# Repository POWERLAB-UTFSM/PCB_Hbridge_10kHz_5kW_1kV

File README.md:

# Proyecto PCB Hbridge

## Descripción

Repositorio con archivos necesarios para visualizar el esquematico y PCB del circuito Hbridge

## Requisitos

### Software

* KiCad, para diseño de esquemático y conversión a placa de circuito impreso
* Git, para control de versiones y manejo de repositorios.

## Contenido de carpetas:

* [PCB_Hbridge](PCB_Hbridge): Carpeta con archivos relacionados al esquematico y 
    * [BOM](PCB_Hbridge/BOM): Carpeta con lista detallada de todos los componentes electrónicos necesarios para construir un circuito impreso (PCB) obtenida directamente desde el software.
    * [GERBER](PCB_Hbridge/GERBER): Carpeta con archivos necesarios para la fabricación de la PCB.

* [BOM_v1](BOM_v1): Lista detallada con los componentes y su precio, dando un estimado del presupuesto necesario para su fabricación.

* [Documento_de_diseno](Documento_de_diseno): Documento que respalda el diseño y desarrollo del circuito implementado en la PCB

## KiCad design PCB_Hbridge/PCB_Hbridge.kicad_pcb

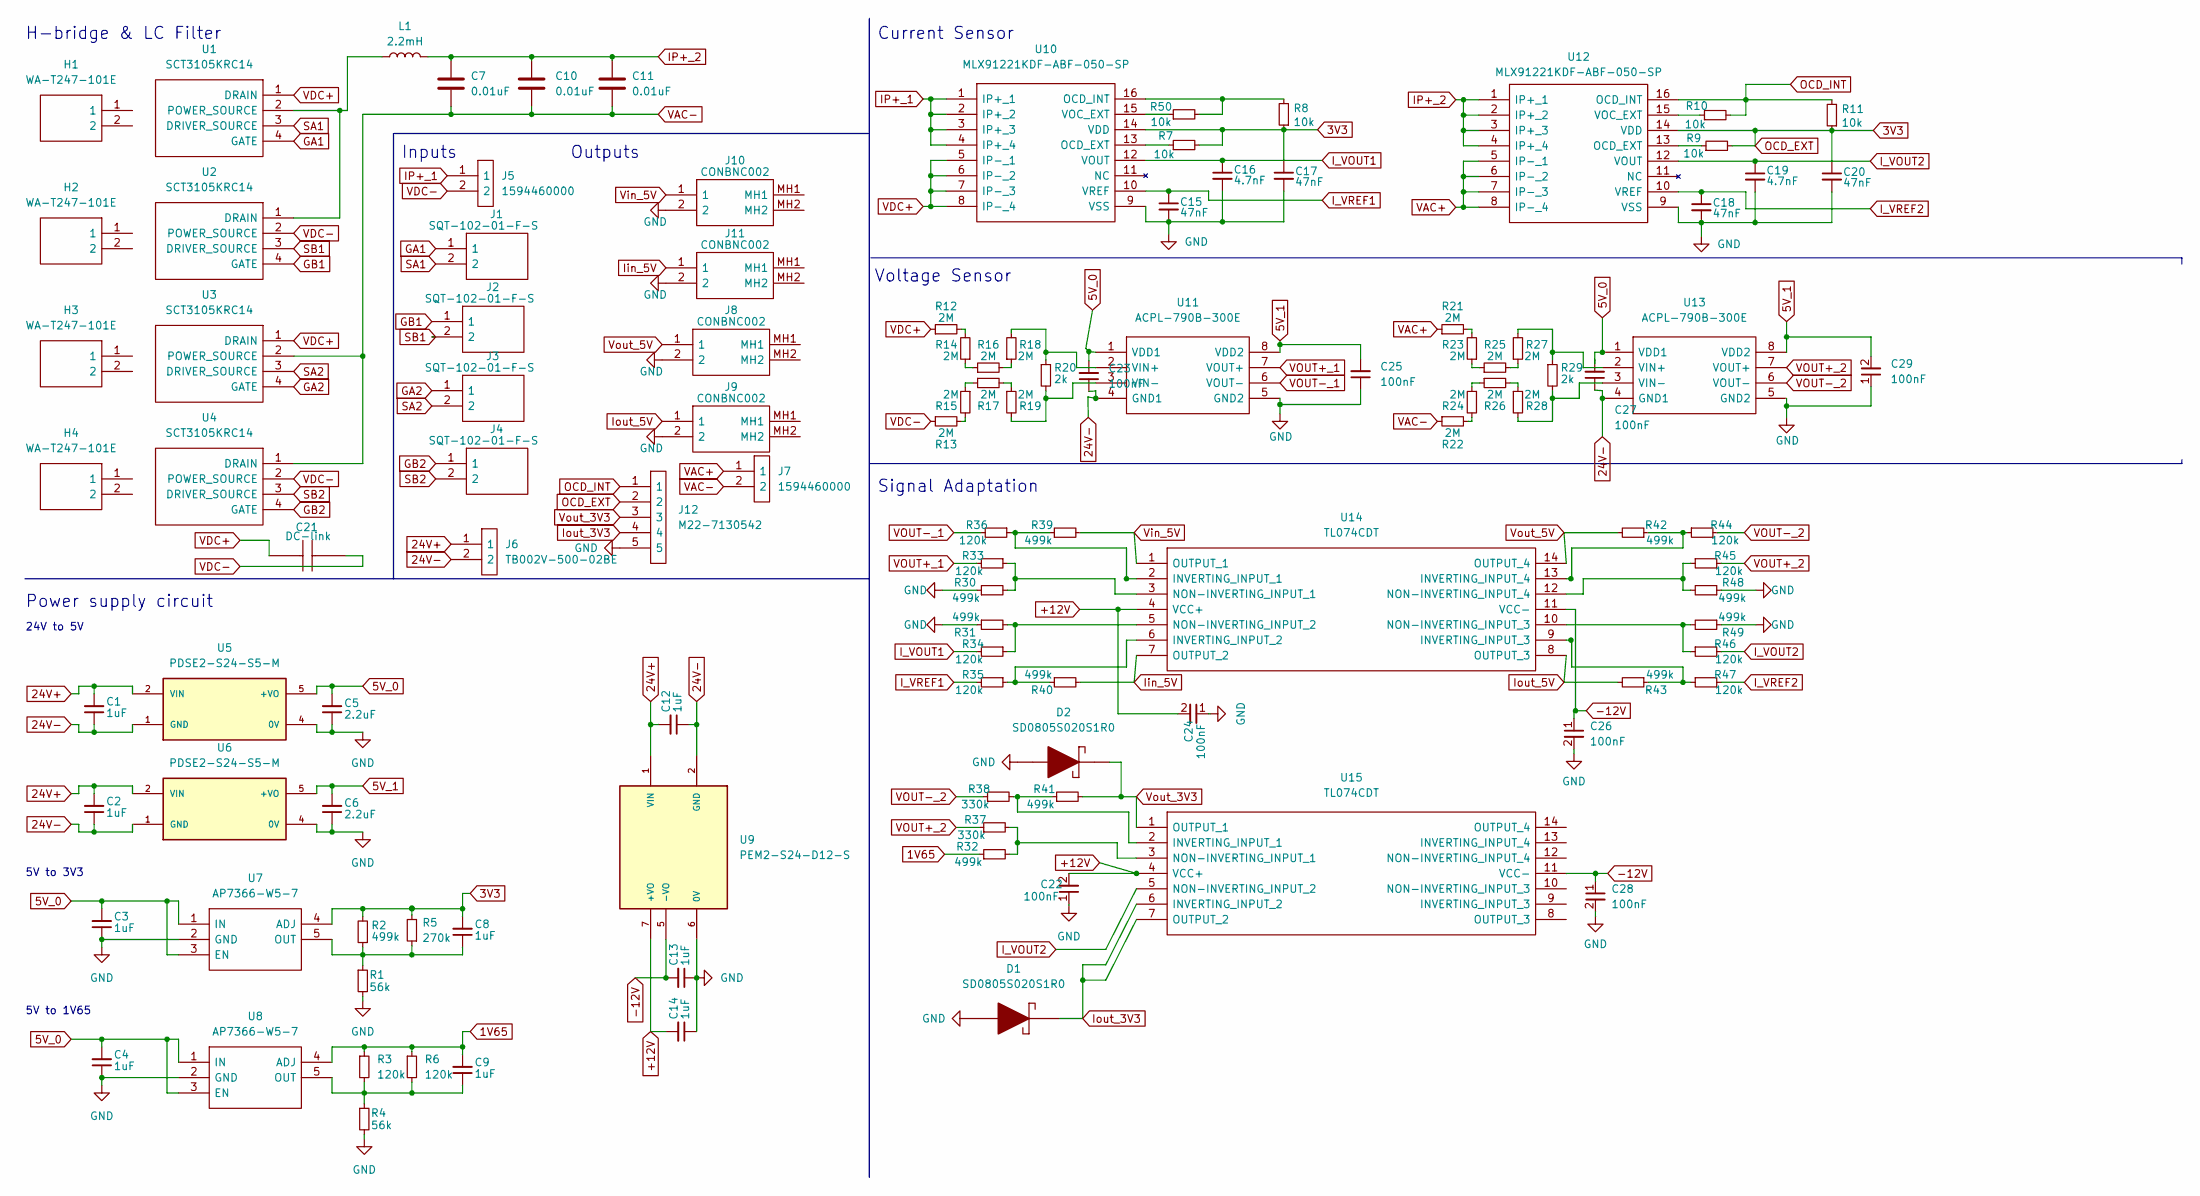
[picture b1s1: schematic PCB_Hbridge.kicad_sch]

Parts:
C1, C2, C3, C4, C8, C9, C12, C13, C14: 1uF; CAPC2012X145N_01uF; Manufacturer_Part_Number AC0805KFX7R9BB105
C5, C6: 2.2uF; CAPC3116X180N_2_2uF; Mouser Part Number 81-GCM31CR71H225KA5K
C7, C10, C11: 0.01uF; S103M69Z5UP63K7R
C15, C17, C18, C20: 47nF; CAPC3216X175N_47nF; Mouser Part Number 80-C1206C561KDGAUTO
C16, C19: 4.7nF; CAPC2012X94N_4_7nF; Mouser Part Number 581-0805ZC472KAT2A
C21: DC-link; C2225_DCLINK; Mouser Part Number 80-C2225C104KFR
C22, C23, C24, C25, C26, C27, C28, C29: 100nF; CAPC1005X55N_100nF; Mouser Part Number 810-CGA2B3X7R1V104K
D1, D2: SD0805S020S1R0; DIOM1613X100N; Mouser Part Number 581-SD0805S020S1R0
H1, H2, H3, H4: WA-T247-101E; WAT247101E; Mouser Part Number 588-WA-T247-101E
J1, J2, J3, J4: SQT-102-01-F-S; SQT-102-01-XX-S; Mouser Part Number 200-SQT10201FS
J5, J7: 1594460000; Mouser Part Number 470-1594460000
J6: TB002V-500-02BE; TB002V50002BE; Mouser Part Number 490-TB002V-500-02BE
J8, J9, J10, J11: CONBNC002; Mouser Part Number 712-CONBNC002
J12: M22-7130542; RHDR5W50P0X200_1X5_1050X240X440P; Mouser Part Number 855-M22-7130542
L1: 2.2mH; L_Toroid_Horizontal_D69.1mm_P63.20mm_Vishay_TJ9; Manufacturer_Part_Number TJ92UEB222L; Mouser Path Number 70-TJ92UEB222L
R1, R4: 56k; RESC2012X60N_56k; Mouser Part Number 652-CR0805FX-5602ELF
R2, R30, R31, R32, R39, R40, R41, R42, R43, R48, R49: 499k; RESC2012X60N_499k; Mouser Part Number 652-CR0805FX-5602ELF
R3, R6, R33, R34, R35, R36, R44, R45, R46, R47: 120k; RESC2012X50N_120k; Mouser Part Number 652-CR0805FX-5602ELF
R5: 270k; RESC2012X50N_270k; Mouser Part Number 652-CR0805FX-5602ELF
R7, R8, R10, R11, R50: 10k; RESC2012X60N_10k; Mouser Part Number 652-CR0805FX-1002ELF
R9: 10k; RESC2012X60N_10k
R12, R13, R14, R15, R16, R17, R18, R19, R21, R22, R23, R24, R25, R26, R27, R28: 2M; RESC6332X70N_2M; Mouser Part Number 71-RCV25122M00FKEGAT
R20, R29: 2k; RESC3216X65N_2k; Manufacturer_Part_Number SFR18EZPJ202
R37, R38: 330k; ERJUP3_330k; Mouser Part Number 667-ERJ-UP3F3303V
U1, U2, U3, U4: SCT3105KRC14; Mouser Part Number 755-SCT3105KRC14
U5, U6: PDSE2-S24-S5-M; CONV_PDSE2-S24-S5-M; PARTREV 1.0
U7, U8: AP7366-W5-7; SOT95P285X140-5N; Mouser Part Number 621-AP7366-W5-7
U9: PEM2-S24-D12-S; CONV_PEM2-S24-D12-S
U10, U12: MLX91221KDF-ABF-050-SP; SOIC127P1031X264-16N; Manufacturer_Part_Number MLX91221KDF-ABF-050-SP; Mouser Part Number 482-91221KDFABF050SP
U11, U13: ACPL-790B-300E; DIP762W65P254L980H470Q8N; Mouser Part Number 630-ACPL-790B-300E
U14, U15: TL074CDT; SOIC127P600X175-14N_TL074; Mouser Part Number 511-TL074CDT

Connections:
1V65: C9.2, R3.1, R6.1, R32.1, U8.4 (ADJ)
3V3: C8.2, C17.1, C20.1, J12.2, R2.2, R5.2, R7.2, R8.1, R9.2, R11.1, U7.4 (ADJ), U10.14 (VDD), U12.14 (VDD)
5V_0: C3.2, C4.2, C5.2, C23.2, C27.2, U5.5 (+VO), U7.1 (IN), U7.3 (EN), U8.1 (IN), U8.3 (EN), U11.1 (VDD1), U13.1 (VDD1)
5V_1: C6.2, C25.2, C29.2, U6.5 (+VO), U11.8 (VDD2), U13.8 (VDD2)
24V+: C1.2, C2.2, C12.2, J6.1, U5.2 (VIN), U6.2 (VIN), U9.1 (VIN)
24V-: C1.1, C2.1, C12.1, C23.1, C27.1, J6.2, U5.1 (GND), U6.1 (GND), U9.2 (GND), U11.4 (GND1), U13.4 (GND1)
+12V: C14.2, C22.2, C24.2, U9.7 (+VO), U14.4 (VCC+), U15.4 (VCC+)
-12V: C13.2, C26.1, C28.1, U9.5 (-VO), U14.11 (VCC-), U15.11 (VCC-)
GA1: J1.1, U1.4 (GATE)
GA2: J3.1, U3.4 (GATE)
GB1: J2.1, U2.4 (GATE)
GB2: J4.1, U4.4 (GATE)
GND: C3.1, C4.1, C5.1, C6.1, C13.1, C14.1, C15.2, C16.2, C17.2, C18.2, C19.2, C20.2, C22.1, C24.1, C25.1, C26.2, C28.2, C29.1, D1.2, D2.2, J8.2, J9.2, J10.2, J11.2, J12.5, R1.2, R4.2, R30.1, R31.1, R48.1, R49.1, U5.4 (0V), U6.4 (0V), U7.2 (GND), U8.2 (GND), U9.6 (0V), U10.9 (VSS), U11.5 (GND2), U12.9 (VSS), U13.5 (GND2)
IP+_1: J5.1, U10.1 (IP+_1), U10.2 (IP+_2), U10.3 (IP+_3), U10.4 (IP+_4)
IP+_2: C7.1, C10.1, C11.2, L1.2, U12.1 (IP+_1), U12.2 (IP+_2), U12.3 (IP+_3), U12.4 (IP+_4)
I_VOUT1: C16.1, R34.2, U10.12 (VOUT)
I_VOUT2: C19.1, R46.2, U12.12 (VOUT), U15.5 (NON-INVERTING_INPUT_2)
I_VREF1: C15.1, R35.2, U10.10 (VREF)
I_VREF2: C18.1, R47.2, U12.10 (VREF)
Iin_5V: J11.1, R40.2, U14.7 (OUTPUT_2)
Iout_3V3: D1.1, J12.4, U15.6 (INVERTING_INPUT_2), U15.7 (OUTPUT_2)
Iout_5V: J9.1, R43.2, U14.8 (OUTPUT_3)
unnamed: C8.1, R1.1, R2.1, R5.1, U7.5 (OUT)
unnamed: C9.1, R3.2, R4.1, R6.2, U8.5 (OUT)
unnamed: R12.2, R14.2
unnamed: R13.2, R15.2
unnamed: R14.1, R16.1
unnamed: R15.1, R17.1
unnamed: R16.2, R18.1
unnamed: R17.2, R19.1
unnamed: R21.2, R23.2
unnamed: R22.2, R24.2
unnamed: R23.1, R25.1
unnamed: R24.1, R26.1
unnamed: R25.2, R27.1
unnamed: R26.2, R28.1
unnamed: R32.2, R37.2, U15.3 (NON-INVERTING_INPUT_1)
unnamed: R38.2, R41.1, U15.2 (INVERTING_INPUT_1)
unnamed: L1.1, U1.2 (POWER_SOURCE), U2.1 (DRAIN)
unnamed: R7.1, U10.13 (OCD_EXT)
unnamed: R50.1, U10.15 (VOC_EXT)
unnamed: R8.2, R50.2, U10.16 (OCD_INT)
unnamed: R18.2, R20.1, U11.2 (VIN+)
unnamed: R19.2, R20.2, U11.3 (VIN-)
unnamed: R9.1, U12.13 (OCD_EXT)
unnamed: R10.1, U12.15 (VOC_EXT)
unnamed: R27.2, R29.1, U13.2 (VIN+)
unnamed: R28.2, R29.2, U13.3 (VIN-)
unnamed: R36.1, R39.1, U14.2 (INVERTING_INPUT_1)
unnamed: R30.2, R33.1, U14.3 (NON-INVERTING_INPUT_1)
unnamed: R31.2, R34.1, U14.5 (NON-INVERTING_INPUT_2)
unnamed: R35.1, R40.1, U14.6 (INVERTING_INPUT_2)
unnamed: R43.1, R47.1, U14.9 (INVERTING_INPUT_3)
unnamed: R46.1, R49.2, U14.10 (NON-INVERTING_INPUT_3)
unnamed: R45.1, R48.2, U14.12 (NON-INVERTING_INPUT_4)
unnamed: R42.1, R44.1, U14.13 (INVERTING_INPUT_4)
OCD_INT: J12.1, R10.2, R11.2, U12.16 (OCD_INT)
SA1: J1.2, U1.3 (DRIVER_SOURCE)
SA2: J3.2, U3.3 (DRIVER_SOURCE)
SB1: J2.2, U2.3 (DRIVER_SOURCE)
SB2: J4.2, U4.3 (DRIVER_SOURCE)
VAC+: J7.1, R21.1, U12.5 (IP-_1), U12.6 (IP-_2), U12.7 (IP-_3), U12.8 (IP-_4)
VAC-: C7.2, C10.2, C11.1, J7.2, R22.1, U3.2 (POWER_SOURCE), U4.1 (DRAIN)
VDC+: C21.1, R12.1, U1.1 (DRAIN), U3.1 (DRAIN), U10.5 (IP-_1), U10.6 (IP-_2), U10.7 (IP-_3), U10.8 (IP-_4)
VDC-: C21.2, J5.2, R13.1, U2.2 (POWER_SOURCE), U4.2 (POWER_SOURCE)
VOUT+_1: R33.2, U11.7 (VOUT+)
VOUT+_2: R37.1, R45.2, U13.7 (VOUT+)
VOUT-_1: R36.2, U11.6 (VOUT-)
VOUT-_2: R38.1, R44.2, U13.6 (VOUT-)
Vin_5V: J10.1, R39.2, U14.1 (OUTPUT_1)
Vout_3V3: D2.1, J12.3, R41.2, U15.1 (OUTPUT_1)
Vout_5V: J8.1, R42.2, U14.14 (OUTPUT_4)

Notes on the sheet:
Power supply circuit
24V to 5V
Outputs
Current Sensor
5V to 1V65
Signal Adaptation
5V to 3V3
Inputs
H-bridge & LC Filter
Voltage Sensor

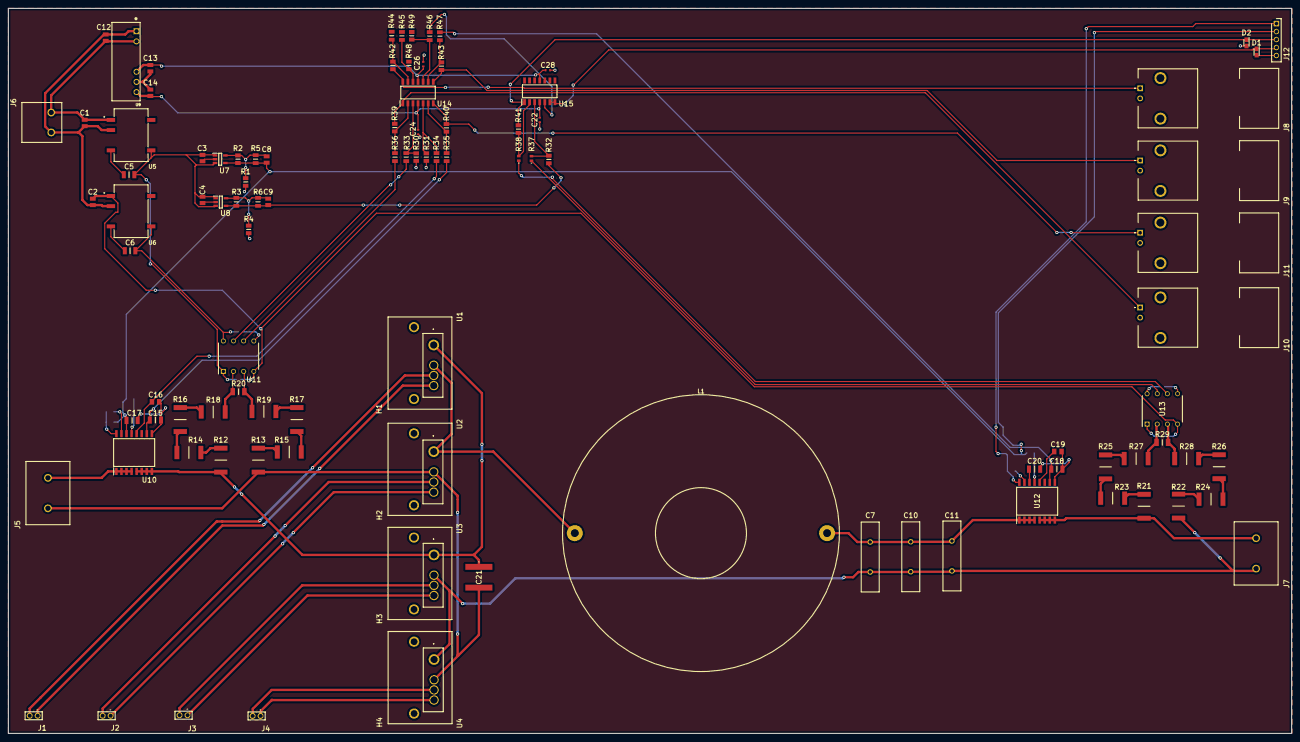
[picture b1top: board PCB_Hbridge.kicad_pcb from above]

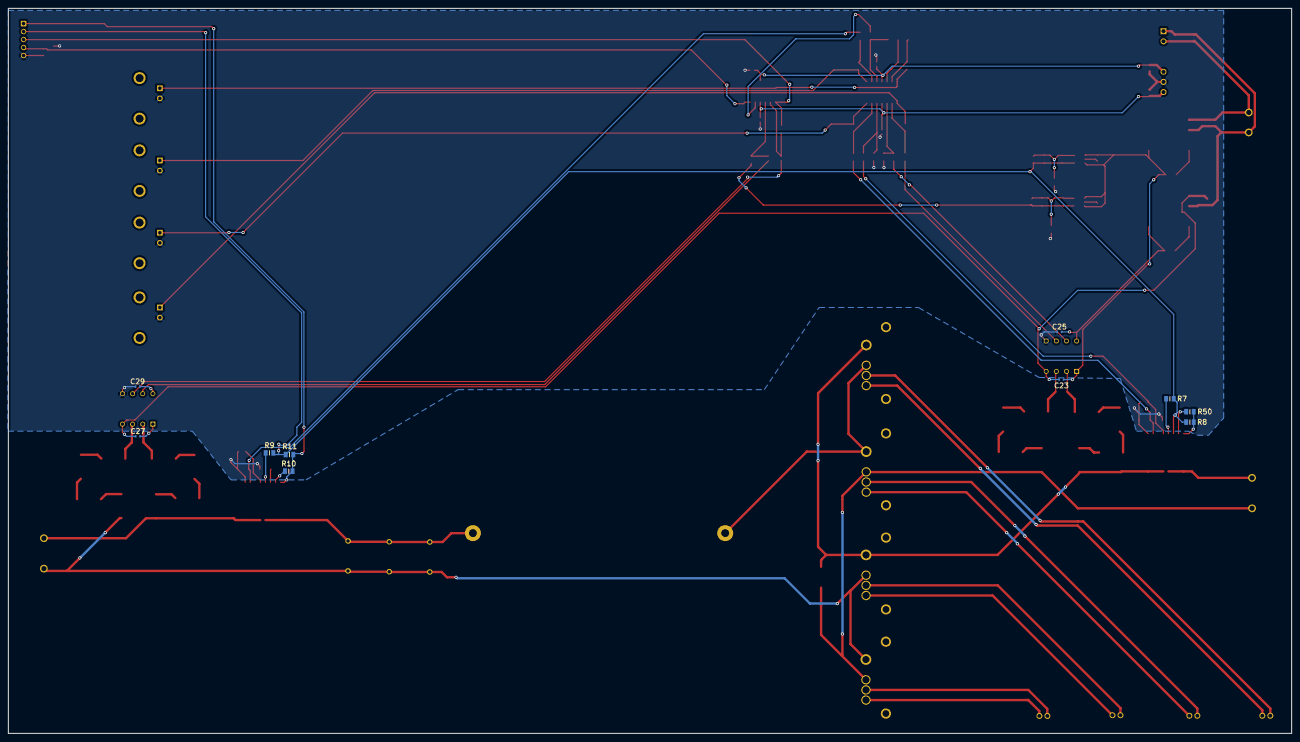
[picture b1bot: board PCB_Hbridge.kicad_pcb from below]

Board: 2 copper layers, 321.4 x 181.6 mm, 113 parts (10 on the bottom side), 72 nets.

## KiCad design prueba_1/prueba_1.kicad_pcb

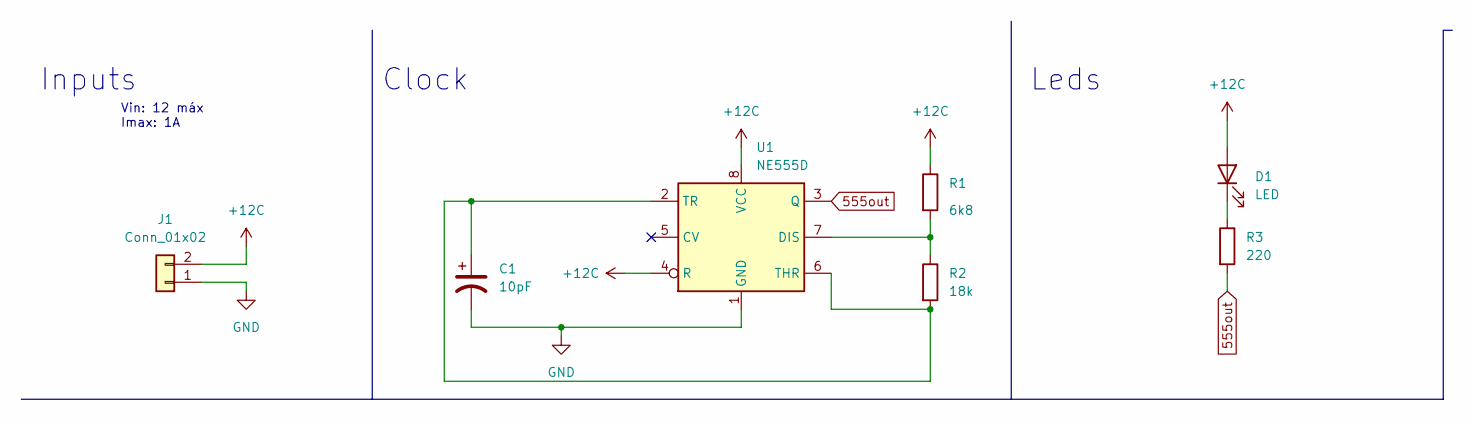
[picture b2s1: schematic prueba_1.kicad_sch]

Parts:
C1: 10pF; CP_Radial_D10.0mm_P3.80mm
D1: LED; LED_D5.0mm_FlatTop
J1: Conn_01x02; TerminalBlock_bornier-2_P5.08mm
R1: 6k8; R_1206_3216Metric
R2: 18k; R_1206_3216Metric
R3: 220; R_1206_3216Metric
U1: NE555D; SOIC-8_3.9x4.9mm_P1.27mm

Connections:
555out: R3.2, U1.3 (Q)
+12C: D1.2 (A), J1.2, R1.1, U1.4 (R), U1.8 (VCC)
GND: C1.2, J1.1, U1.1 (GND)
unnamed: C1.1, R2.2, U1.2 (TR), U1.6 (THR)
unnamed: D1.1 (K), R3.1
unnamed: R1.2, R2.1, U1.7 (DIS)

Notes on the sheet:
Clock
Vin: 12 máx Imax: 1A
Inputs
Leds

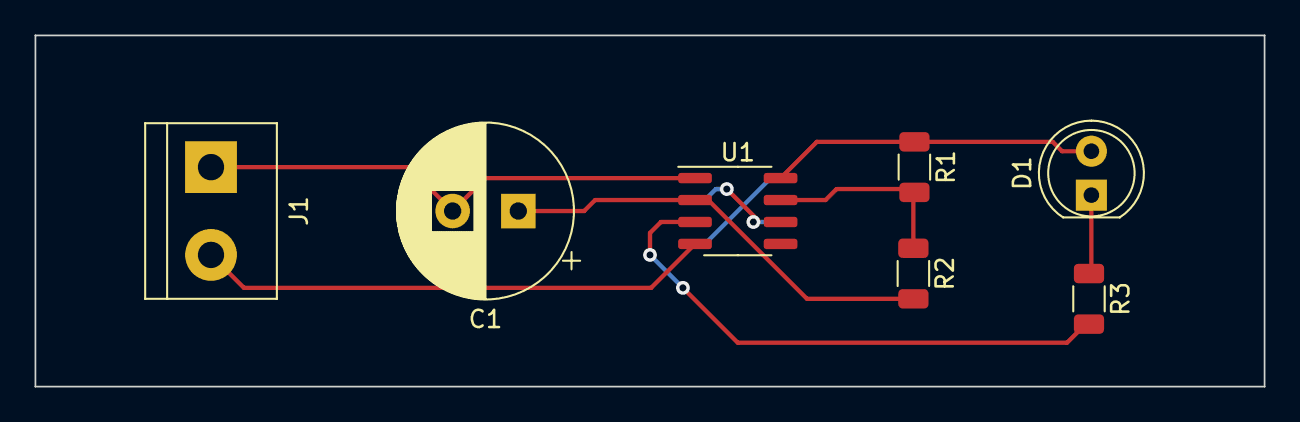
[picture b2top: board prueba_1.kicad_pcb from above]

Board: 2 copper layers, 71.1 x 20.3 mm, 7 parts (0 on the bottom side), 6 nets.

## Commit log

2023-01-23 first time
2023-02-01 Presupuesto estimado
2023-03-13 Add files via upload
    Documentación del desarrollo de la PCB.
